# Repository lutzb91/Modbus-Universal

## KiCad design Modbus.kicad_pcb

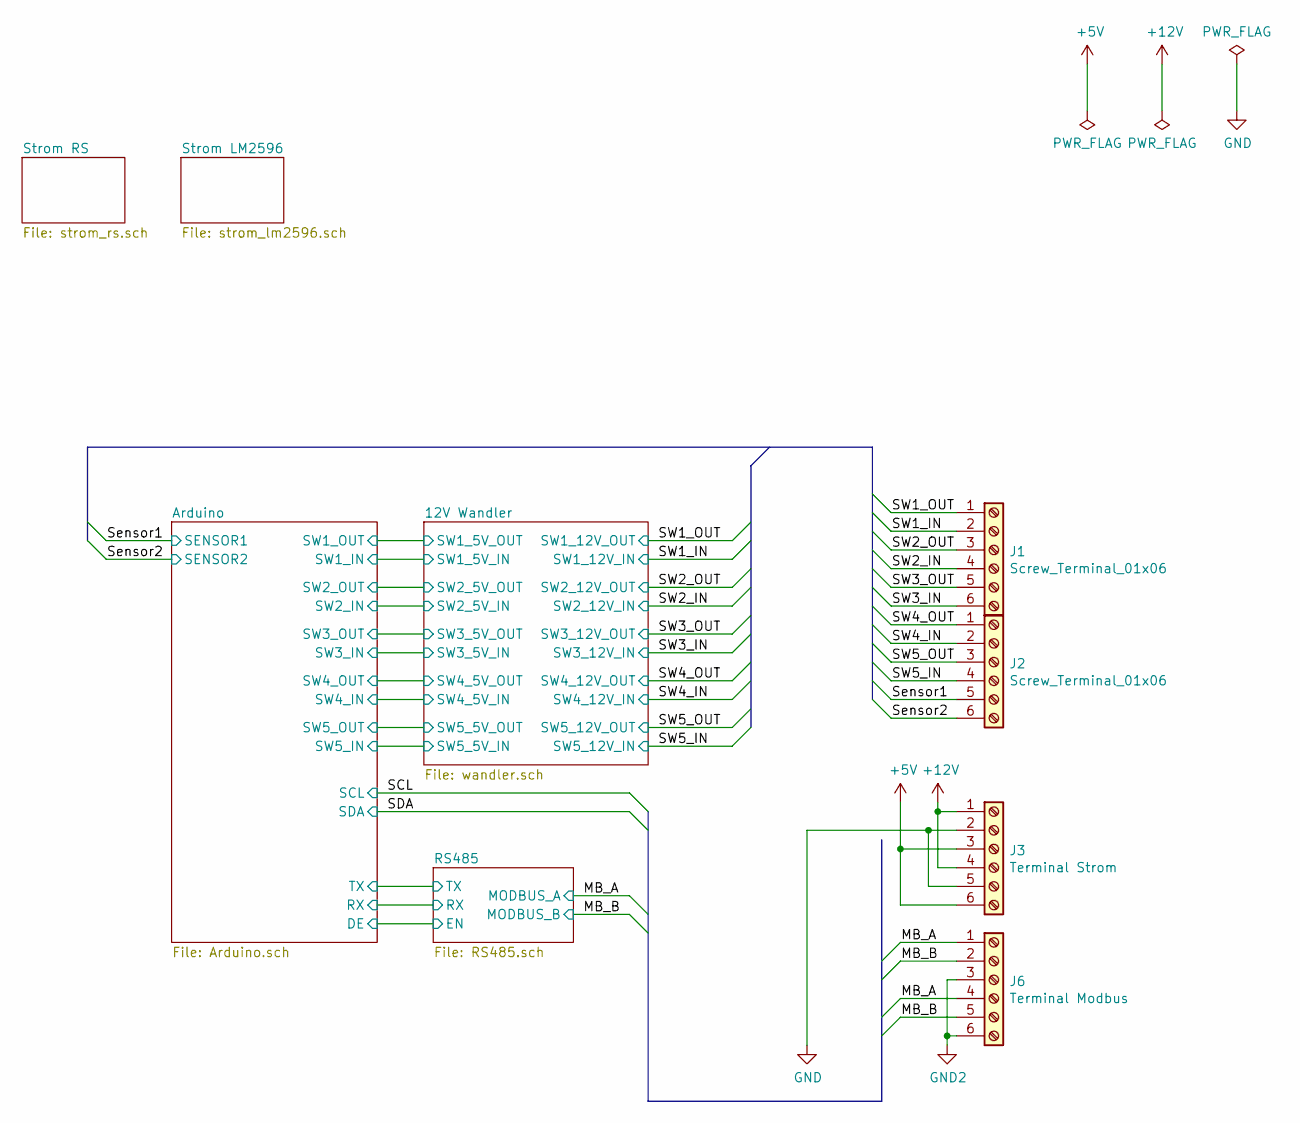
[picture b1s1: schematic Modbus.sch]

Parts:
J1, J2: Screw_Terminal_01x06; TerminalBlock_Phoenix_MKDS-1,5-6_1x06_P5.00mm_Horizontal
J3: Terminal Strom; TerminalBlock_Phoenix_MKDS-1,5-6_1x06_P5.00mm_Horizontal
J6: Terminal Modbus; TerminalBlock_Phoenix_MKDS-1,5-6_1x06_P5.00mm_Horizontal

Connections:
+5V: J3.3, J3.6; also elsewhere on the board
+12V: J3.1, J3.4; also elsewhere on the board
/MB_A: J6.1, J6.4; also elsewhere on the board
/MB_B: J6.2, J6.5; also elsewhere on the board
/SW1_IN: J1.2; also elsewhere on the board
/SW1_OUT: J1.1; also elsewhere on the board
/SW2_IN: J1.4; also elsewhere on the board
/SW2_OUT: J1.3; also elsewhere on the board
/SW3_IN: J1.6; also elsewhere on the board
/SW3_OUT: J1.5; also elsewhere on the board
/SW4_IN: J2.2; also elsewhere on the board
/SW4_OUT: J2.1; also elsewhere on the board
/SW5_IN: J2.4; also elsewhere on the board
/SW5_OUT: J2.3; also elsewhere on the board
/Sensor1: J2.5; also elsewhere on the board
/Sensor2: J2.6; also elsewhere on the board
GND: J3.2, J3.5; also elsewhere on the board
GND2: J6.3, J6.6; also elsewhere on the board

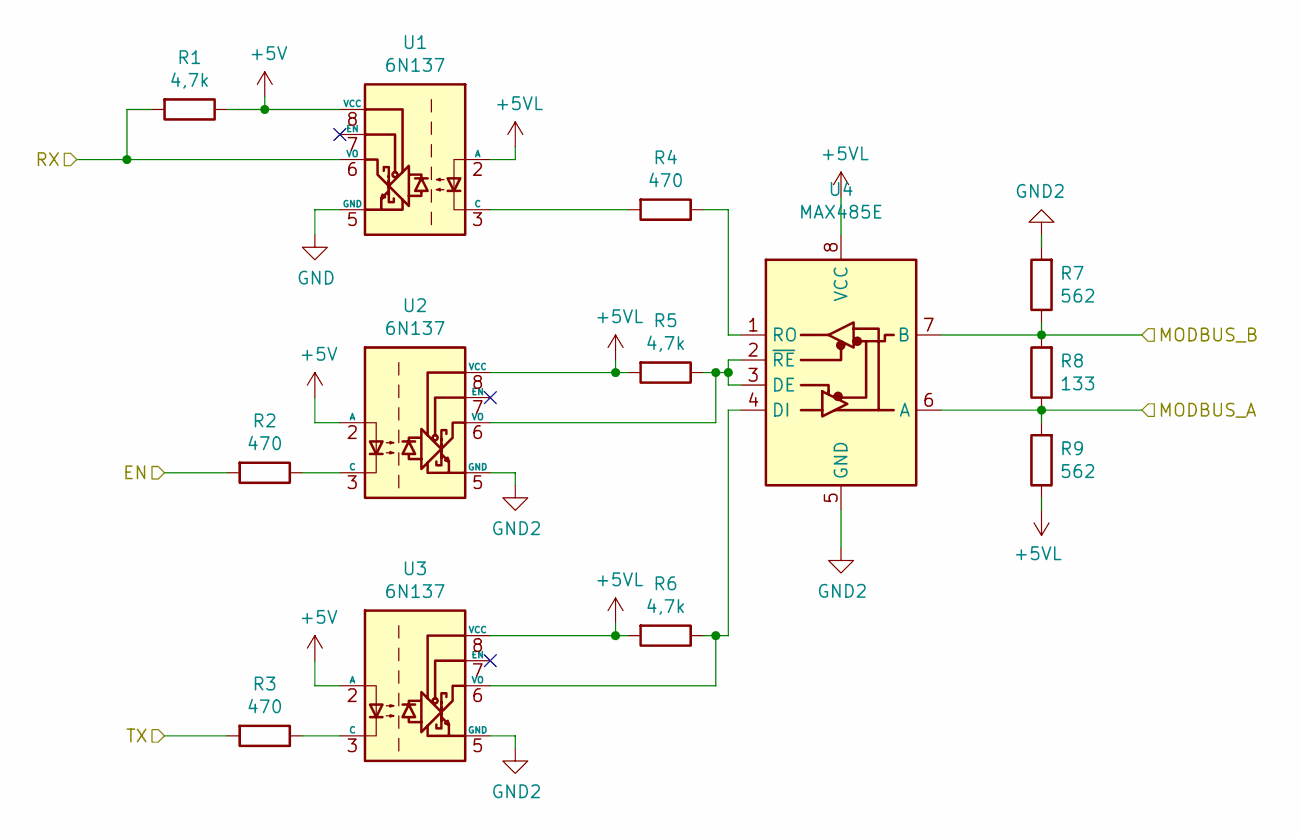
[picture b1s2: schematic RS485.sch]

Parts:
R1, R5, R6: 4,7k; R_0805_2012Metric_Pad1.15x1.40mm_HandSolder
R2, R3, R4: 470; R_0805_2012Metric_Pad1.15x1.40mm_HandSolder
R7, R9: 562; R_0805_2012Metric_Pad1.15x1.40mm_HandSolder
R8: 133; R_0805_2012Metric_Pad1.15x1.40mm_HandSolder
U1, U2, U3: 6N137; DIP-8_W8.89mm_SMDSocket_LongPads
U4: MAX485E; SOIC-8-1EP_3.9x4.9mm_P1.27mm_EP2.29x3mm

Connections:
+5V: R1.1, U1.8 (VCC), U2.2 (A), U3.2 (A); also elsewhere on the board
+5VL: R5.2, R6.2, R9.1, U1.2 (A), U2.8 (VCC), U3.8 (VCC), U4.8 (VCC); also elsewhere on the board
/Arduino/DE: R2.2; also elsewhere on the board
/Arduino/RX: R1.2, U1.6 (VO); also elsewhere on the board
/Arduino/TX: R3.2; also elsewhere on the board
/MB_A: R8.1, R9.2, U4.6 (A); also elsewhere on the board
/MB_B: R7.1, R8.2, U4.7 (B); also elsewhere on the board
GND: U1.5 (GND); also elsewhere on the board
GND2: R7.2, U2.5 (GND), U3.5 (GND), U4.5 (GND); also elsewhere on the board
unnamed: R2.1, U2.3 (C)
unnamed: R3.1, U3.3 (C)
unnamed: R4.1, U4.1 (RO)
unnamed: R4.2, U1.3 (C)
unnamed: R5.1, U2.6 (VO), U4.2 (~RE), U4.3 (DE)
unnamed: R6.1, U3.6 (VO), U4.4 (DI)

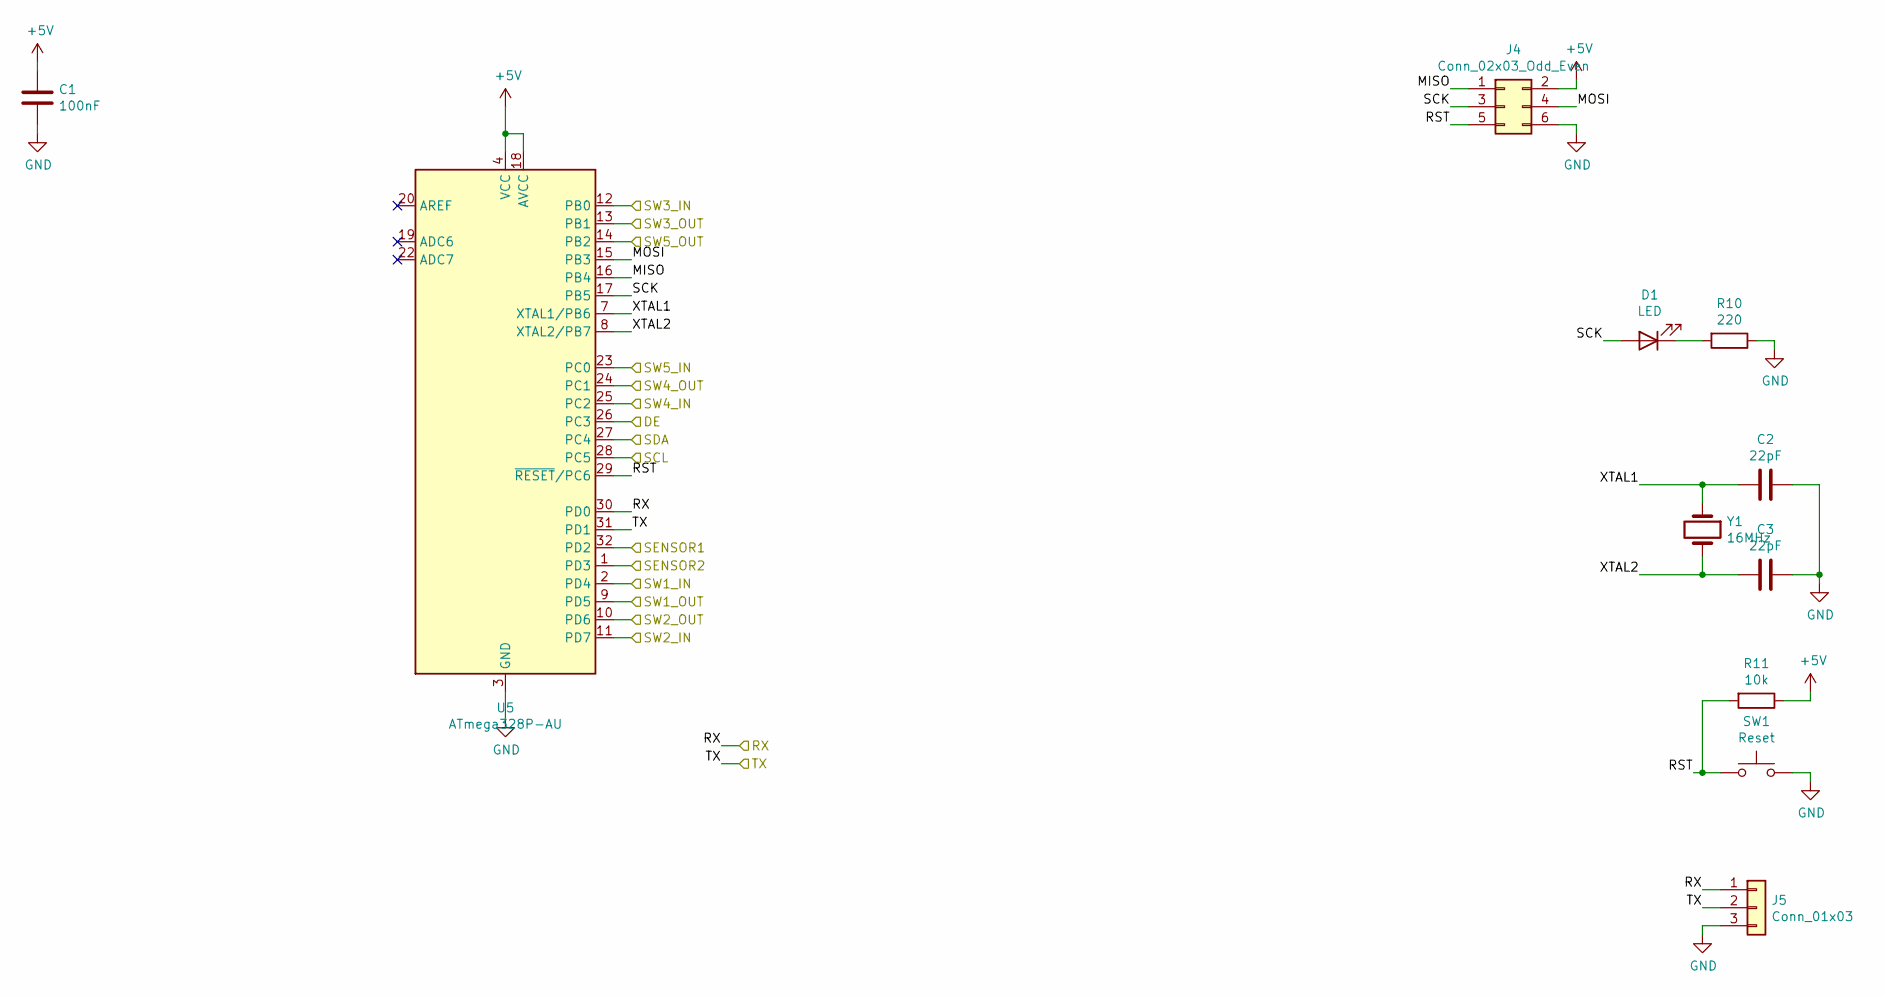
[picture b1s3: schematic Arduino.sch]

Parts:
C1: 100nF; C_0805_2012Metric_Pad1.15x1.40mm_HandSolder
C2, C3: 22pF; C_0805_2012Metric_Pad1.15x1.40mm_HandSolder
D1: LED; LED_0805_2012Metric_Pad1.15x1.40mm_HandSolder
J4: Conn_02x03_Odd_Even; PinHeader_2x03_P2.54mm_Vertical
J5: Conn_01x03; PinHeader_1x03_P2.54mm_Vertical
R10: 220; R_0805_2012Metric_Pad1.15x1.40mm_HandSolder
R11: 10k; R_0805_2012Metric_Pad1.15x1.40mm_HandSolder
SW1: Reset; SW_SPST_FSMSM
U5: ATmega328P-AU; TQFP-32_7x7mm_P0.8mm
Y1: 16MHz; Crystal_SMD_HC49-SD_HandSoldering

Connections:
+5V: C1.1, J4.2, R11.1, U5.4 (VCC), U5.6 (VCC), U5.18 (AVCC); also elsewhere on the board
/12V Wandler/SW1_5V_IN: U5.2 (PD4); also elsewhere on the board
/12V Wandler/SW1_5V_OUT: U5.9 (PD5); also elsewhere on the board
/12V Wandler/SW2_5V_IN: U5.11 (PD7); also elsewhere on the board
/12V Wandler/SW2_5V_OUT: U5.10 (PD6); also elsewhere on the board
/12V Wandler/SW3_5V_IN: U5.12 (PB0); also elsewhere on the board
/12V Wandler/SW3_5V_OUT: U5.13 (PB1); also elsewhere on the board
/12V Wandler/SW4_5V_IN: U5.25 (PC2); also elsewhere on the board
/12V Wandler/SW4_5V_OUT: U5.24 (PC1); also elsewhere on the board
/12V Wandler/SW5_5V_IN: U5.23 (PC0); also elsewhere on the board
/12V Wandler/SW5_5V_OUT: U5.14 (PB2); also elsewhere on the board
/Arduino/DE: U5.26 (PC3); also elsewhere on the board
/Arduino/MISO: J4.1, U5.16 (PB4); also elsewhere on the board
/Arduino/MOSI: J4.4, U5.15 (PB3); also elsewhere on the board
/Arduino/RST: J4.5, R11.2, SW1.1, U5.29 (~RESET~/PC6); also elsewhere on the board
/Arduino/RX: J5.1, U5.30 (PD0); also elsewhere on the board
/Arduino/SCK: D1.2 (A), J4.3, U5.17 (PB5); also elsewhere on the board
/Arduino/TX: J5.2, U5.31 (PD1); also elsewhere on the board
/Arduino/XTAL1: C2.2, U5.7 (XTAL1/PB6), Y1.1
/Arduino/XTAL2: C3.2, U5.8 (XTAL2/PB7), Y1.2
/SCL: U5.28 (PC5)
/SDA: U5.27 (PC4)
/Sensor1: U5.32 (PD2); also elsewhere on the board
/Sensor2: U5.1 (PD3); also elsewhere on the board
GND: C1.2, C2.1, C3.1, J4.6, J5.3, R10.1, SW1.2, U5.3 (GND), U5.5 (GND), U5.21 (GND); also elsewhere on the board
unnamed: D1.1 (K), R10.2

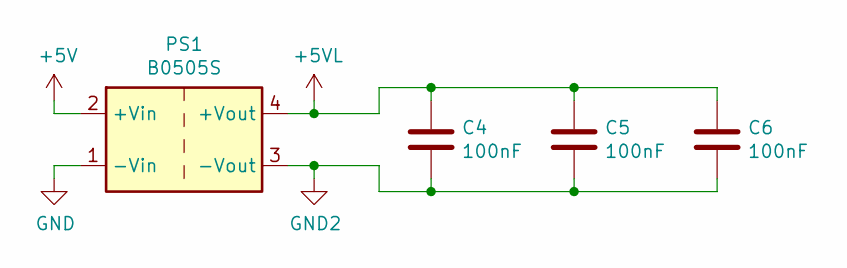
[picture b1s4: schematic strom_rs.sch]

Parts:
C4, C5, C6: 100nF; C_0805_2012Metric_Pad1.15x1.40mm_HandSolder
PS1: B0505S; Converter_DCDC_Murata_MEE1SxxxxSC_THT

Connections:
+5V: PS1.2 (+Vin); also elsewhere on the board
+5VL: C4.1, C5.1, C6.1, PS1.4 (+Vout); also elsewhere on the board
GND: PS1.1 (-Vin); also elsewhere on the board
GND2: C4.2, C5.2, C6.2, PS1.3 (-Vout); also elsewhere on the board

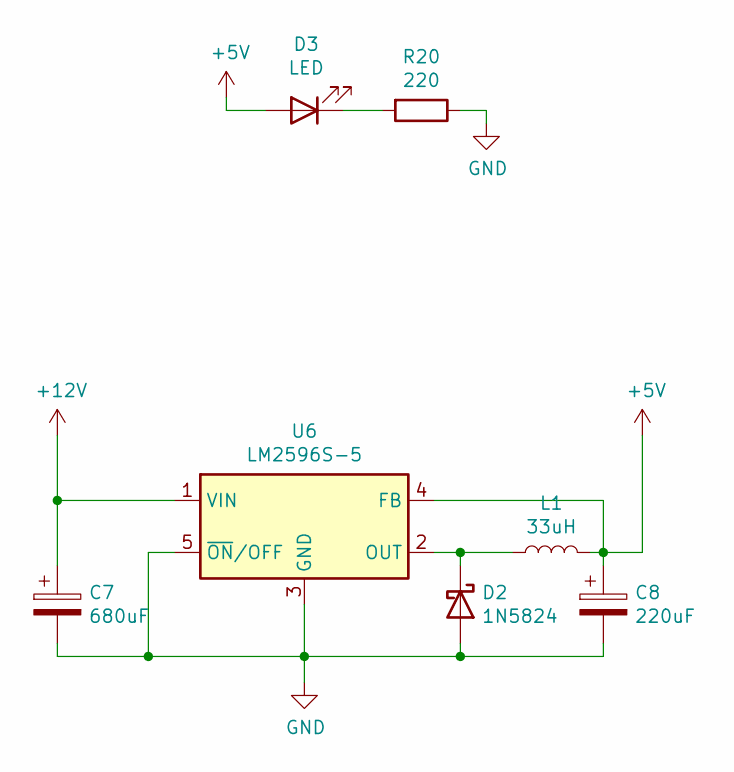
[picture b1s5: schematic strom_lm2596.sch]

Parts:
C7: 680uF; CP_Radial_D10.0mm_P5.00mm
C8: 220uF; CP_Radial_D6.3mm_P2.50mm
D2: 1N5824; D_SMA_Handsoldering
D3: LED; LED_0805_2012Metric_Pad1.15x1.40mm_HandSolder
L1: 33uH; L_Radial_D7.0mm_P3.00mm
R20: 220; R_0805_2012Metric_Pad1.15x1.40mm_HandSolder
U6: LM2596S-5; TO-263-5_TabPin3

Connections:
+5V: C8.1, D3.2 (A), L1.2, U6.4 (FB); also elsewhere on the board
+12V: C7.1, U6.1 (VIN); also elsewhere on the board
GND: C7.2, C8.2, D2.2 (A), R20.1, U6.3 (GND), U6.5 (~ON~/OFF); also elsewhere on the board
unnamed: D2.1 (K), L1.1, U6.2 (OUT)
unnamed: D3.1 (K), R20.2

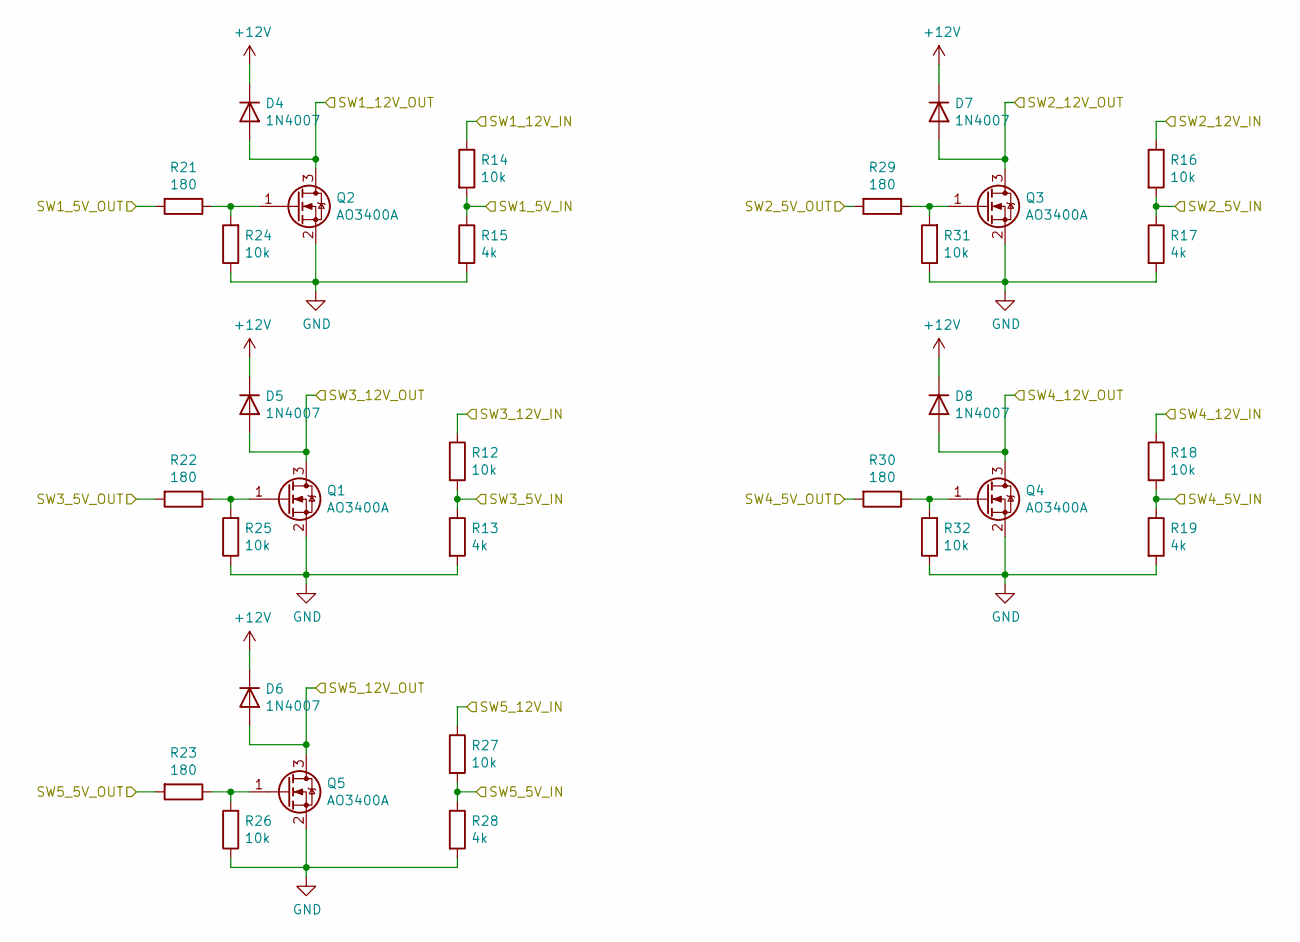
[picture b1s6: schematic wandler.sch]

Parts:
D4, D5, D6, D7, D8: 1N4007; D_SMA_Handsoldering
Q1, Q2, Q3, Q4, Q5: AO3400A; SOT-23_Handsoldering
R12, R14, R16, R18, R24, R25, R26, R27, R31, R32: 10k; R_0805_2012Metric_Pad1.15x1.40mm_HandSolder
R13, R15, R17, R19, R28: 4k; R_0805_2012Metric_Pad1.15x1.40mm_HandSolder
R21, R22, R23, R29, R30: 180; R_0805_2012Metric_Pad1.15x1.40mm_HandSolder

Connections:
+12V: D4.1 (K), D5.1 (K), D6.1 (K), D7.1 (K), D8.1 (K); also elsewhere on the board
/12V Wandler/SW1_5V_IN: R14.2, R15.1; also elsewhere on the board
/12V Wandler/SW1_5V_OUT: R21.2; also elsewhere on the board
/12V Wandler/SW2_5V_IN: R16.2, R17.1; also elsewhere on the board
/12V Wandler/SW2_5V_OUT: R29.2; also elsewhere on the board
/12V Wandler/SW3_5V_IN: R12.2, R13.1; also elsewhere on the board
/12V Wandler/SW3_5V_OUT: R22.2; also elsewhere on the board
/12V Wandler/SW4_5V_IN: R18.2, R19.1; also elsewhere on the board
/12V Wandler/SW4_5V_OUT: R30.2; also elsewhere on the board
/12V Wandler/SW5_5V_IN: R27.2, R28.1; also elsewhere on the board
/12V Wandler/SW5_5V_OUT: R23.2; also elsewhere on the board
/SW1_IN: R14.1; also elsewhere on the board
/SW1_OUT: D4.2 (A), Q2.3 (D); also elsewhere on the board
/SW2_IN: R16.1; also elsewhere on the board
/SW2_OUT: D7.2 (A), Q3.3 (D); also elsewhere on the board
/SW3_IN: R12.1; also elsewhere on the board
/SW3_OUT: D5.2 (A), Q1.3 (D); also elsewhere on the board
/SW4_IN: R18.1; also elsewhere on the board
/SW4_OUT: D8.2 (A), Q4.3 (D); also elsewhere on the board
/SW5_IN: R27.1; also elsewhere on the board
/SW5_OUT: D6.2 (A), Q5.3 (D); also elsewhere on the board
GND: Q1.2 (S), Q2.2 (S), Q3.2 (S), Q4.2 (S), Q5.2 (S), R13.2, R15.2, R17.2, R19.2, R24.1, R25.1, R26.1, R28.2, R31.1, R32.1; also elsewhere on the board
unnamed: Q1.1 (G), R22.1, R25.2
unnamed: Q2.1 (G), R21.1, R24.2
unnamed: Q3.1 (G), R29.1, R31.2
unnamed: Q4.1 (G), R30.1, R32.2
unnamed: Q5.1 (G), R23.1, R26.2

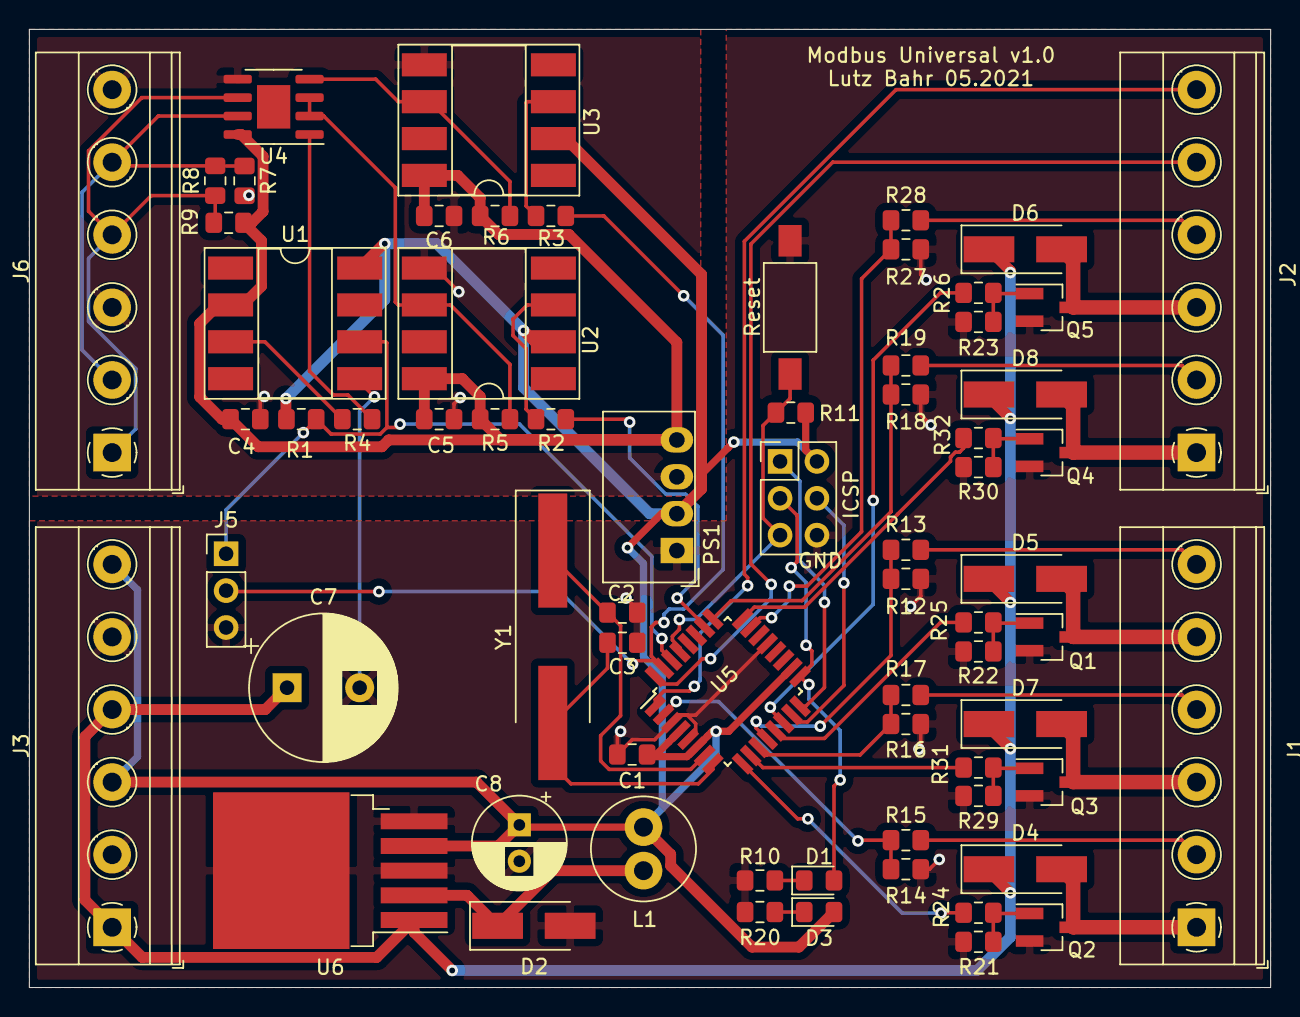
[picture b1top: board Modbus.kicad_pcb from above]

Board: 2 copper layers, 85.5 x 66.0 mm, 69 parts (0 on the bottom side), 52 nets.

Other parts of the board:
ICSP: Conn_02x03_Odd_Even; PinHeader_2x03_P2.54mm_Vertical
Reset: Reset; SW_SPST_FSMSM

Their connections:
+5V: ICSP.2; also elsewhere on the board
/Arduino/MISO: ICSP.1; also elsewhere on the board
/Arduino/MOSI: ICSP.4; also elsewhere on the board
/Arduino/RST: ICSP.5, Reset.1; also elsewhere on the board
/Arduino/SCK: ICSP.3; also elsewhere on the board
GND: ICSP.6, Reset.2; also elsewhere on the board

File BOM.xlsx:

Item | Qty | Reference(s) | Value | LibPart | Footprint
1 | 4 | C1, C4, C5, C6 | 100nF | Device:C | Capacitor_SMD:C_0805_2012Metric_Pad1.15x1.40mm_HandSolder
2 | 2 | C2, C3 | 22pF | Device:C | Capacitor_SMD:C_0805_2012Metric_Pad1.15x1.40mm_HandSolder
3 | 1 | C7 | 680uF | Device:CP | Capacitor_THT:CP_Radial_D10.0mm_P5.00mm
4 | 1 | C8 | 220uF | Device:CP | Capacitor_THT:CP_Radial_D6.3mm_P2.50mm
5 | 2 | D1, D3 | LED | Device:LED | LED_SMD:LED_0805_2012Metric_Pad1.15x1.40mm_HandSolder
6 | 1 | D2 | 1N5824 | Device:D_Schottky | Diode_SMD:D_SMA_Handsoldering
7 | 5 | D4, D5, D6, D7, D8 | 1N4007 | Device:D | Diode_SMD:D_SMA_Handsoldering
8 | 2 | J1, J2 | Screw_Terminal_01x06 | Connector:Screw_Terminal_01x06 | TerminalBlock_Phoenix:TerminalBlock_Phoenix_MKDS-1,5-6_1x06_P5.00mm_Horizontal
9 | 1 | J3 | Terminal Strom | Connector:Screw_Terminal_01x06 | TerminalBlock_Phoenix:TerminalBlock_Phoenix_MKDS-1,5-6_1x06_P5.00mm_Horizontal
10 | 1 | J4 | Conn_02x03_Odd_Even | Connector_Generic:Conn_02x03_Odd_Even | Connector_PinHeader_2.54mm:PinHeader_2x03_P2.54mm_Vertical
11 | 1 | J5 | Conn_01x03 | Connector_Generic:Conn_01x03 | Connector_PinHeader_2.54mm:PinHeader_1x03_P2.54mm_Vertical
12 | 1 | J6 | Terminal Modbus | Connector:Screw_Terminal_01x06 | TerminalBlock_Phoenix:TerminalBlock_Phoenix_MKDS-1,5-6_1x06_P5.00mm_Horizontal
13 | 1 | L1 | 33uH | Device:L | Inductor_THT:L_Radial_D7.0mm_P3.00mm
14 | 1 | PS1 | B0505S | Converter_DCDC:MEE1S0505SC | Converter_DCDC:Converter_DCDC_Murata_MEE1SxxxxSC_THT
15 | 5 | Q1, Q2, Q3, Q4, Q5 | AO3400A | Transistor_FET:AO3400A | Package_TO_SOT_SMD:SOT-23_Handsoldering
16 | 3 | R1, R5, R6 | 4,7k | Device:R | Resistor_SMD:R_0805_2012Metric_Pad1.15x1.40mm_HandSolder
17 | 3 | R2, R3, R4 | 470 | Device:R | Resistor_SMD:R_0805_2012Metric_Pad1.15x1.40mm_HandSolder
18 | 2 | R7, R9 | 562 | Device:R | Resistor_SMD:R_0805_2012Metric_Pad1.15x1.40mm_HandSolder
19 | 1 | R8 | 133 | Device:R | Resistor_SMD:R_0805_2012Metric_Pad1.15x1.40mm_HandSolder
20 | 2 | R10, R20 | 220 | Device:R | Resistor_SMD:R_0805_2012Metric_Pad1.15x1.40mm_HandSolder
21 | 11 | R11, R12, R14, R16, R18, R24, R25, R26, R27, R31, R32 | 10k | Device:R | Resistor_SMD:R_0805_2012Metric_Pad1.15x1.40mm_HandSolder
22 | 5 | R13, R15, R17, R19, R28 | 4k | Device:R | Resistor_SMD:R_0805_2012Metric_Pad1.15x1.40mm_HandSolder
23 | 5 | R21, R22, R23, R29, R30 | 180 | Device:R | Resistor_SMD:R_0805_2012Metric_Pad1.15x1.40mm_HandSolder
24 | 1 | SW1 | Reset | Switch:SW_Push | Button_Switch_SMD:SW_SPST_FSMSM
25 | 3 | U1, U2, U3 | 6N137 | Isolator:6N137 | Package_DIP:DIP-8_W8.89mm_SMDSocket_LongPads
26 | 1 | U4 | MAX485E | Interface_UART:MAX485E | Package_SO:SOIC-8-1EP_3.9x4.9mm_P1.27mm_EP2.29x3mm
27 | 1 | U5 | ATmega328P-AU | MCU_Microchip_ATmega:ATmega328P-AU | Package_QFP:TQFP-32_7x7mm_P0.8mm
28 | 1 | U6 | LM2596S-5 | Regulator_Switching:LM2596S-5 | Package_TO_SOT_SMD:TO-263-5_TabPin3
29 | 1 | Y1 | 16MHz | Device:Crystal | Crystal:Crystal_SMD_HC49-SD_HandSoldering

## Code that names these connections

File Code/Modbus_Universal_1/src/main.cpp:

#include <Arduino.h>
#include <Modbus.h>
#include <ModbusSerial.h>
#include "Output.h"

#define PIN_SW1_IN     4
#define PIN_SW2_IN     7
#define PIN_SW3_IN     8
#define PIN_SW4_IN    A2
#define PIN_SW5_IN    A0

#define PIN_SW1_OUT    5
#define PIN_SW2_OUT    6
#define PIN_SW3_OUT    9
#define PIN_SW4_OUT   A1
#define PIN_SW5_OUT   10

#define PIN_SENSOR1    2
#define PIN_SENSOR2    3

#define PIN_RS485_DE  A3

#define NUM_SWITCH     5


ModbusSerial mb;

Output outputs[NUM_SWITCH];

void setup() {

  mb.config(&Serial, 38400, SERIAL_8N1, PIN_RS485_DE);
  mb.setSlaveId(11);

  pinMode(13, OUTPUT);
  digitalWrite(13, LOW);

  outputs[0].begin(PIN_SW1_OUT, PIN_SW1_IN, &mb);
  outputs[1].begin(PIN_SW2_OUT, PIN_SW2_IN, &mb, 1);
  outputs[2].begin(PIN_SW3_OUT, PIN_SW3_IN, &mb, 2);
  outputs[3].begin(PIN_SW4_OUT, PIN_SW4_IN, &mb, 3);
  outputs[4].begin(PIN_SW5_OUT, PIN_SW5_IN, &mb, 4);
}

void loop() {
  mb.task();
  for(int i=0;i<NUM_SWITCH;i++) {
    outputs[i].task();
  }
}

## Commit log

2021-05-19 Code hinzugefuegt
